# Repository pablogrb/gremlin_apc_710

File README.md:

# Gremlin APC 710

Hardware design repository for the Gremlin APC 710 project, containing:
- FreeCAD mechanical design files in [CAD](CAD)
- KiCAD electronics design files in [EDA](EDA)

## GitHub Repository

Project repository:
https://github.com/pablogrb/gremlin_apc_710

## Repository Structure

- [CAD](CAD)
  - FreeCAD source models (`.FCStd`)
  - Mechanical export files (for example `.step`)
- [EDA](EDA)
  - KiCAD schematic (`.kicad_sch`)
  - KiCAD PCB layout (`.kicad_pcb`)
  - KiCAD project files (`.kicad_pro`)

## Project Instructions

- CAD instructions: [docs/CAD_instructions.md](docs/CAD_instructions.md)
- EDA instructions: [docs/EDA_instructions.md](docs/EDA_instructions.md)

## Tooling

- Mechanical CAD: FreeCAD V1.1.0
- Electronic design: KiCAD V9.0.6

## Version Control Notes

This repository is configured to ignore temporary and machine-local artifacts generated by FreeCAD, KiCAD, and macOS (for example backup files, lock files, cache files, and `.DS_Store`).

## Font Licenses

Fonts used by this project are documented with folder-local license notes:

- [CAD/TTF/LICENSE.txt](CAD/TTF/LICENSE.txt)
- [EDA/TTF/LICENSE.txt](EDA/TTF/LICENSE.txt)

Current tracked font files include:

- CAD/TTF/DejaVuSansCondensed-Bold.ttf
- EDA/TTF/bamf.ttf

Important licensing note:
The Bamf font license (see [EDA/TTF/LICENSE.txt](EDA/TTF/LICENSE.txt)) states free use for non-commercial use and requires separate terms for commercial use.

## License

This project is licensed under the Creative Commons Attribution-NonCommercial 3.0 license.

See [LICENSE.md](LICENSE.md) for the dedicated license file.

License text and details:
https://creativecommons.org/licenses/by-nc/3.0/

Unless otherwise noted in specific files or directories, project content is distributed under this license.

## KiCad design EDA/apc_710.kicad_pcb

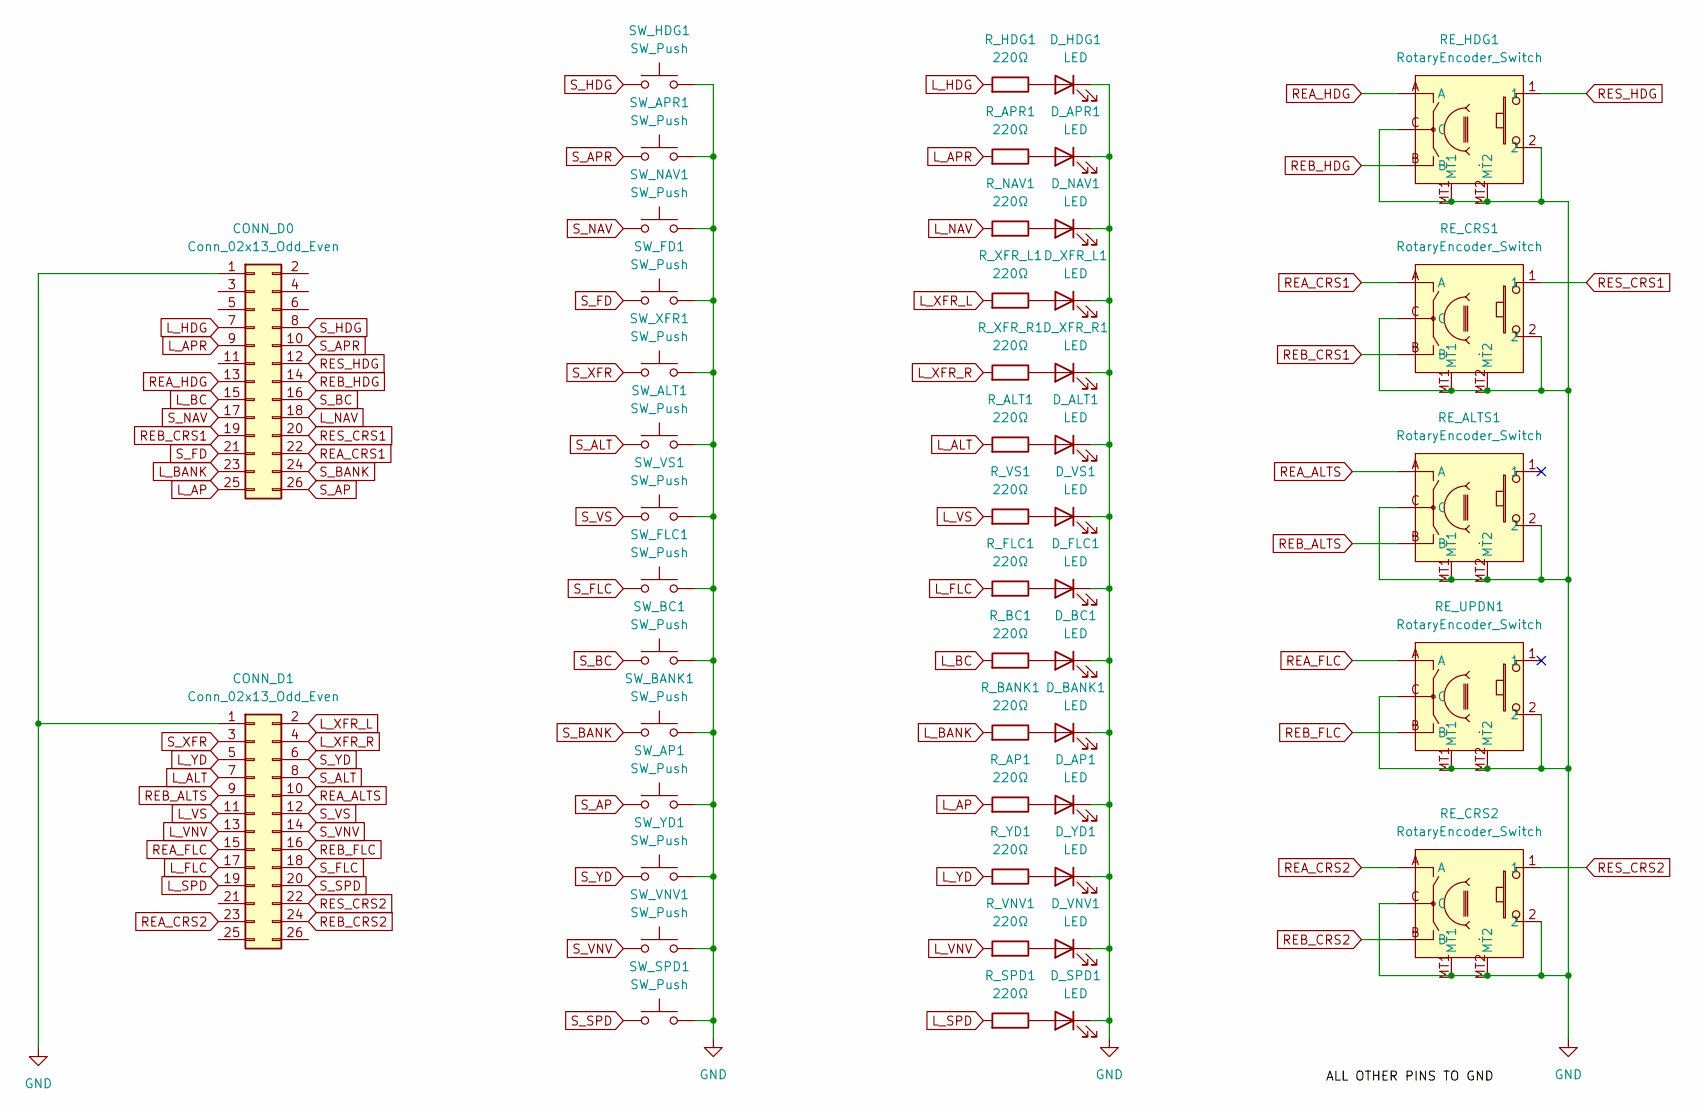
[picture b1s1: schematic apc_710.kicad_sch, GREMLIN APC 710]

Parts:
CONN_D0, CONN_D1: Conn_02x13_Odd_Even; IDC-Header_2x13_P2.54mm_Vertical
D_ALT1: LED; LED_Rectangular_W3.0mm_H2.0mm
D_AP1: LED; LED_Rectangular_W3.0mm_H2.0mm
D_APR1: LED; LED_Rectangular_W3.0mm_H2.0mm
D_BANK1: LED; LED_Rectangular_W3.0mm_H2.0mm
D_BC1: LED; LED_Rectangular_W3.0mm_H2.0mm
D_FLC1: LED; LED_Rectangular_W3.0mm_H2.0mm
D_HDG1: LED; LED_Rectangular_W3.0mm_H2.0mm
D_NAV1: LED; LED_Rectangular_W3.0mm_H2.0mm
D_SPD1: LED; LED_Rectangular_W3.0mm_H2.0mm
D_VNV1: LED; LED_Rectangular_W3.0mm_H2.0mm
D_VS1: LED; LED_Rectangular_W3.0mm_H2.0mm
D_XFR_L1: LED; LED_Rectangular_W3.0mm_H2.0mm
D_XFR_R1: LED; LED_Rectangular_W3.0mm_H2.0mm
D_YD1: LED; LED_Rectangular_W3.0mm_H2.0mm
RE_ALTS1: RotaryEncoder_Switch; SW-TH_PEC11H-4020F-S0016; LCSC Part C22402656
RE_CRS1, RE_CRS2: RotaryEncoder_Switch; SW-TH_PEC11H-4020F-S0016; LCSC Part C22402656
RE_HDG1: RotaryEncoder_Switch; SW-TH_PEC11H-4020F-S0016; LCSC Part C22402656
RE_UPDN1: RotaryEncoder_Switch; SW-TH_PEC11H-4020F-S0016; LCSC Part C22402656
R_ALT1: 220Ω; R_Axial_DIN0207_L6.3mm_D2.5mm_P7.62mm_Horizontal
R_AP1: 220Ω; R_Axial_DIN0207_L6.3mm_D2.5mm_P7.62mm_Horizontal
R_APR1: 220Ω; R_Axial_DIN0207_L6.3mm_D2.5mm_P7.62mm_Horizontal
R_BANK1: 220Ω; R_Axial_DIN0207_L6.3mm_D2.5mm_P7.62mm_Horizontal
R_BC1: 220Ω; R_Axial_DIN0207_L6.3mm_D2.5mm_P7.62mm_Horizontal
R_FLC1: 220Ω; R_Axial_DIN0207_L6.3mm_D2.5mm_P7.62mm_Horizontal
R_HDG1: 220Ω; R_Axial_DIN0207_L6.3mm_D2.5mm_P7.62mm_Horizontal
R_NAV1: 220Ω; R_Axial_DIN0207_L6.3mm_D2.5mm_P7.62mm_Horizontal
R_SPD1: 220Ω; R_Axial_DIN0207_L6.3mm_D2.5mm_P7.62mm_Horizontal
R_VNV1: 220Ω; R_Axial_DIN0207_L6.3mm_D2.5mm_P7.62mm_Horizontal
R_VS1: 220Ω; R_Axial_DIN0207_L6.3mm_D2.5mm_P7.62mm_Horizontal
R_XFR_L1: 220Ω; R_Axial_DIN0207_L6.3mm_D2.5mm_P7.62mm_Horizontal
R_XFR_R1: 220Ω; R_Axial_DIN0207_L6.3mm_D2.5mm_P7.62mm_Horizontal
R_YD1: 220Ω; R_Axial_DIN0207_L6.3mm_D2.5mm_P7.62mm_Horizontal
SW_ALT1: SW_Push; SW_PUSH_6mm_H5mm
SW_AP1: SW_Push; SW_PUSH_6mm_H5mm
SW_APR1: SW_Push; SW_PUSH_6mm_H5mm
SW_BANK1: SW_Push; SW_PUSH_6mm_H5mm
SW_BC1: SW_Push; SW_PUSH_6mm_H5mm
SW_FD1: SW_Push; SW_PUSH_6mm_H5mm
SW_FLC1: SW_Push; SW_PUSH_6mm_H5mm
SW_HDG1: SW_Push; SW_PUSH_6mm_H5mm
SW_NAV1: SW_Push; SW_PUSH_6mm_H5mm
SW_SPD1: SW_Push; SW_PUSH_6mm_H5mm
SW_VNV1: SW_Push; SW_PUSH_6mm_H5mm
SW_VS1: SW_Push; SW_PUSH_6mm_H5mm
SW_XFR1: SW_Push; SW_PUSH_6mm_H5mm
SW_YD1: SW_Push; SW_PUSH_6mm_H5mm

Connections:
GND: CONN_D0.1, CONN_D1.1, D_ALT1.1 (K), D_AP1.1 (K), D_APR1.1 (K), D_BANK1.1 (K), D_BC1.1 (K), D_FLC1.1 (K), D_HDG1.1 (K), D_NAV1.1 (K), D_SPD1.1 (K), D_VNV1.1 (K), D_VS1.1 (K), D_XFR_L1.1 (K), D_XFR_R1.1 (K), D_YD1.1 (K), RE_ALTS1.2, RE_ALTS1.C, RE_ALTS1.MT1, RE_ALTS1.MT2, RE_CRS1.2, RE_CRS1.C, RE_CRS1.MT1, RE_CRS1.MT2, RE_CRS2.2, RE_CRS2.C, RE_CRS2.MT1, RE_CRS2.MT2, RE_HDG1.2, RE_HDG1.C, RE_HDG1.MT1, RE_HDG1.MT2, RE_UPDN1.2, RE_UPDN1.C, RE_UPDN1.MT1, RE_UPDN1.MT2, SW_ALT1.2, SW_AP1.2, SW_APR1.2, SW_BANK1.2, SW_BC1.2, SW_FD1.2, SW_FLC1.2, SW_HDG1.2, SW_NAV1.2, SW_SPD1.2, SW_VNV1.2, SW_VS1.2, SW_XFR1.2, SW_YD1.2
L_ALT: CONN_D1.7, R_ALT1.2
L_AP: CONN_D0.25, R_AP1.2
L_APR: CONN_D0.9, R_APR1.2
L_BANK: CONN_D0.23, R_BANK1.2
L_BC: CONN_D0.15, R_BC1.2
L_FLC: CONN_D1.17, R_FLC1.2
L_HDG: CONN_D0.7, R_HDG1.2
L_NAV: CONN_D0.18, R_NAV1.2
L_SPD: CONN_D1.19, R_SPD1.2
L_VNV: CONN_D1.13, R_VNV1.2
L_VS: CONN_D1.11, R_VS1.2
L_XFR_L: CONN_D1.2, R_XFR_L1.2
L_XFR_R: CONN_D1.4, R_XFR_R1.2
L_YD: CONN_D1.5, R_YD1.2
unnamed: D_ALT1.2 (A), R_ALT1.1
unnamed: D_AP1.2 (A), R_AP1.1
unnamed: D_APR1.2 (A), R_APR1.1
unnamed: D_BANK1.2 (A), R_BANK1.1
unnamed: D_BC1.2 (A), R_BC1.1
unnamed: D_FLC1.2 (A), R_FLC1.1
unnamed: D_HDG1.2 (A), R_HDG1.1
unnamed: D_NAV1.2 (A), R_NAV1.1
unnamed: D_SPD1.2 (A), R_SPD1.1
unnamed: D_VNV1.2 (A), R_VNV1.1
unnamed: D_VS1.2 (A), R_VS1.1
unnamed: D_XFR_L1.2 (A), R_XFR_L1.1
unnamed: D_XFR_R1.2 (A), R_XFR_R1.1
unnamed: D_YD1.2 (A), R_YD1.1
REA_ALTS: CONN_D1.10, RE_ALTS1.A
REA_CRS1: CONN_D0.22, RE_CRS1.A
REA_CRS2: CONN_D1.23, RE_CRS2.A
REA_FLC: CONN_D1.15, RE_UPDN1.A
REA_HDG: CONN_D0.13, RE_HDG1.A
REB_ALTS: CONN_D1.9, RE_ALTS1.B
REB_CRS1: CONN_D0.19, RE_CRS1.B
REB_CRS2: CONN_D1.24, RE_CRS2.B
REB_FLC: CONN_D1.16, RE_UPDN1.B
REB_HDG: CONN_D0.14, RE_HDG1.B
RES_CRS1: CONN_D0.20, RE_CRS1.1
RES_CRS2: CONN_D1.22, RE_CRS2.1
RES_HDG: CONN_D0.12, RE_HDG1.1
S_ALT: CONN_D1.8, SW_ALT1.1
S_AP: CONN_D0.26, SW_AP1.1
S_APR: CONN_D0.10, SW_APR1.1
S_BANK: CONN_D0.24, SW_BANK1.1
S_BC: CONN_D0.16, SW_BC1.1
S_FD: CONN_D0.21, SW_FD1.1
S_FLC: CONN_D1.18, SW_FLC1.1
S_HDG: CONN_D0.8, SW_HDG1.1
S_NAV: CONN_D0.17, SW_NAV1.1
S_SPD: CONN_D1.20, SW_SPD1.1
S_VNV: CONN_D1.14, SW_VNV1.1
S_VS: CONN_D1.12, SW_VS1.1
S_XFR: CONN_D1.3, SW_XFR1.1
S_YD: CONN_D1.6, SW_YD1.1

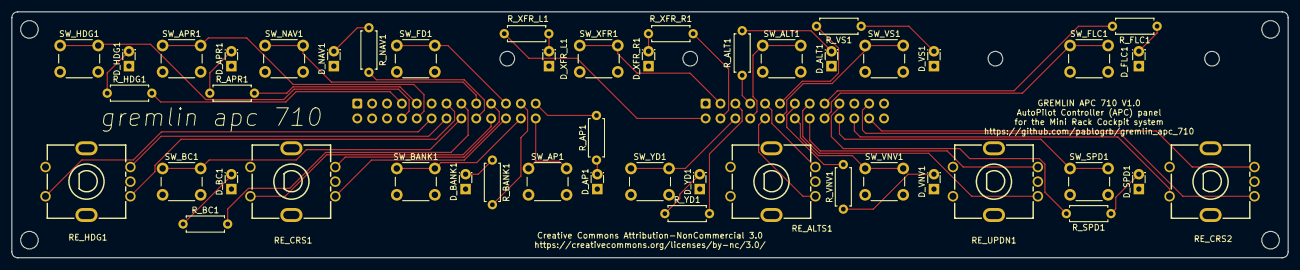
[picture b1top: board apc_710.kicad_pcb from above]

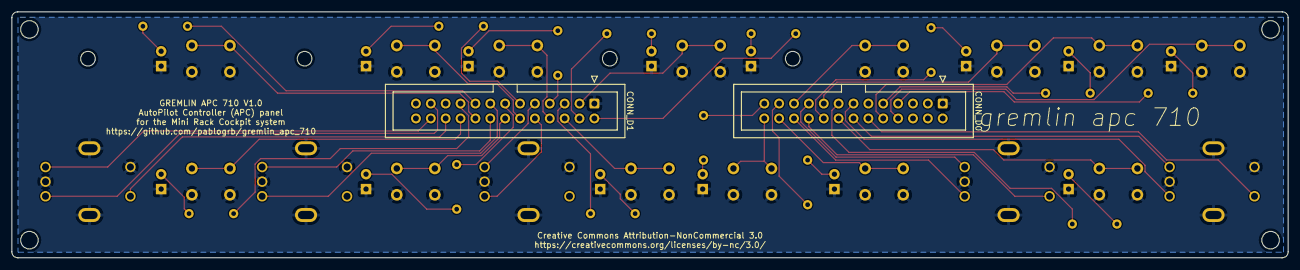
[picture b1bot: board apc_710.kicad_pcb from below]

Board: 2 copper layers, 218.0 x 42.0 mm, 49 parts (2 on the bottom side), 56 nets.

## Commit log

2026-03-31 Initial commit
    CAD and EDA models
    Base readme file
2026-03-31 Updated FreeCAD files to FreeCAD V1.1
2026-03-31 Update README and add CAD instructions with images for APC 710 faceplate and knobs
2026-04-01 renamed EDA files
2026-04-01 GitHub info
    * added exception for schematic lockfiles
    * added github link to readme
    * added github link to pcb, pcb diagram, and schematic diagram
2026-04-01 EDA documentation and BOM
2026-04-01 Add KiCAD generated files and build artifacts to .gitignore
